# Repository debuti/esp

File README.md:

# esp
ESP8266 and ESP32 useful info, first steps and links to resources

Clone with $ git clone --recursive https://github.com/debuti/esp/

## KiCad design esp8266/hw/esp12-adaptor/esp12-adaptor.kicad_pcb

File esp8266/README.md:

# ESP8266 dev instructions
## Hardware used
 * ESP01 w/ 512KB flash
 * ESP01 flash adaptation PCB (green wire one)
 * ESP01 run adaptation PCB (blue and red wires)
 * FTDI cable set to 3.3v
 * USB to miniusb data cable
 * ESP12E w/ 4MB flash
 * ESP12E adaptation PCB
 * ESP12E flash adaptation PCB

## Test that the module is working ok

## Download and build the workenv: toolchain + RTOS SDK
### Download and build the toolchain
```
sudo apt-get install make unrar-free autoconf automake libtool gcc g++ gperf \
    flex bison texinfo gawk ncurses-dev libexpat-dev python-dev python python-serial \
    sed grep git unzip bash help2man wget bzip2 libtool-bin
git clone --recursive https://github.com/pfalcon/esp-open-sdk.git
cd esp-open-sdk
make toolchain esptool libhal STANDALONE=n
echo "export PATH=$PWD/xtensa-lx106-elf/bin:\$PATH" >> ~/.bashrc
cd -
sudo usermod -a -G dialout $USER
```

> You can just install esptool.py if you just plan to flash compiled binaries to esp. sudo pip install esptool

### Download and build the unofficial RTOS SDK
```
git clone --recursive https://github.com/Superhouse/esp-open-rtos.git
cd esp-open-rtos
```
Try to build a sample
```
make -j$(nproc) -C examples/http_get
```

### Download and build the official RTOS SDK
```
git clone https://github.com/espressif/ESP8266_RTOS_SDK.git
```

## Flash!
### ESP12 w/ adaptation pcb
 * Connect jumper in adaptation PCB: GPIO0 -> GND
 * Connect ESP12 to adaptation PCB
 * Connect VCC to 5v with given usb cord
 * Connect FTDI cable to adaptation PCB and to PC
 * Flash with ex: sudo esptool.py --port /dev/ttyUSB0 write_flash 0x00000 <.bin>

### ESP01 w/ flash adaptation pcb
 * Connect ESP01 to adaptation PCB
 * Connect FTDI cable to adaptation PCB and to PC
 * Flash with ex: sudo esptool.py --port /dev/ttyUSB0 write_flash 0x00000 <.bin> 

## Resources
* https://github.com/pfalcon/esp-open-sdk
* https://github.com/Superhouse/esp-open-rtos
* https://github.com/espressif/ESP8266_RTOS_SDK
* http://williamdurand.fr/2015/03/17/playing-with-a-esp8266-wifi-module/
* https://pixhawk.org/_media/peripherals/flashing_esp-01.png

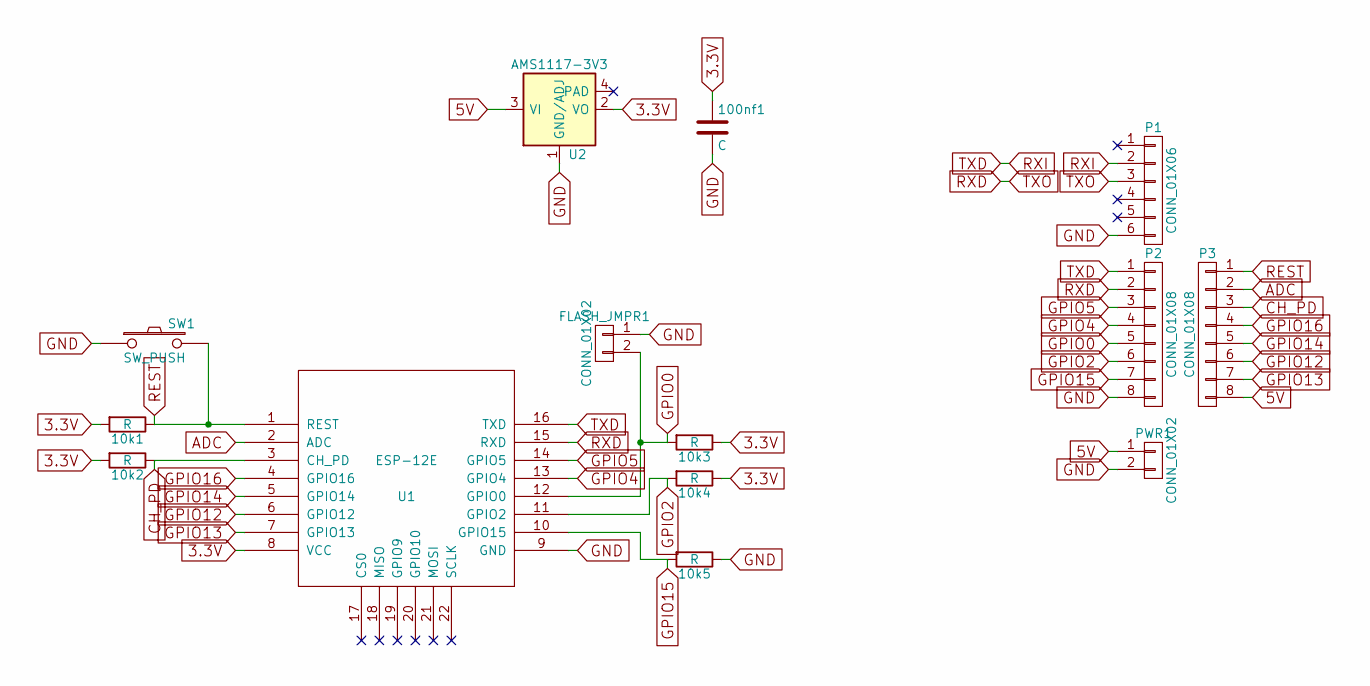
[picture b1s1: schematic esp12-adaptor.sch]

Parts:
10k1, 10k2, 10k3, 10k4, 10k5: R; R_0603_HandSoldering
100nf1: C; C_0603_HandSoldering
FLASH_JMPR1: CONN_01X02; Socket_Strip_Straight_1x02
P1: CONN_01X06; Pin_Header_Angled_1x06
P2, P3: CONN_01X08; Pin_Header_Straight_1x08
PWR1: CONN_01X02; Pin_Header_Straight_1x02
SW1: SW_PUSH; SW_SPST_EVPBF
U1: ESP-12E; ESP-12E_SMD
U2: AMS1117-3V3; SOT-223; MPN LM1117

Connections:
3.3V: 10k1.2, 10k2.2, 10k3.1, 10k4.1, 100nf1.1, U1.8 (VCC), U2.2 (VO)
5V: P3.8, PWR1.1, U2.3 (VI)
ADC: P3.2, U1.2 (ADC)
CH_PD: 10k2.1, P3.3, U1.3 (CH_PD)
GND: 10k5.1, 100nf1.2, FLASH_JMPR1.1, P1.6, P2.8, PWR1.2, SW1.1, U1.9 (GND), U2.1 (GND/ADJ)
GPIO0: 10k3.2, FLASH_JMPR1.2, P2.5, U1.12 (GPIO0)
GPIO2: 10k4.2, P2.6, U1.11 (GPIO2)
GPIO4: P2.4, U1.13 (GPIO4)
GPIO5: P2.3, U1.14 (GPIO5)
GPIO12: P3.6, U1.6 (GPIO12)
GPIO13: P3.7, U1.7 (GPIO13)
GPIO14: P3.5, U1.5 (GPIO14)
GPIO15: 10k5.2, P2.7, U1.10 (GPIO15)
GPIO16: P3.4, U1.4 (GPIO16)
REST: 10k1.1, P3.1, SW1.2, U1.1 (REST)
RXD: P1.3, P2.2, U1.15 (RXD)
RXI: P1.2, P2.1, U1.16 (TXD)

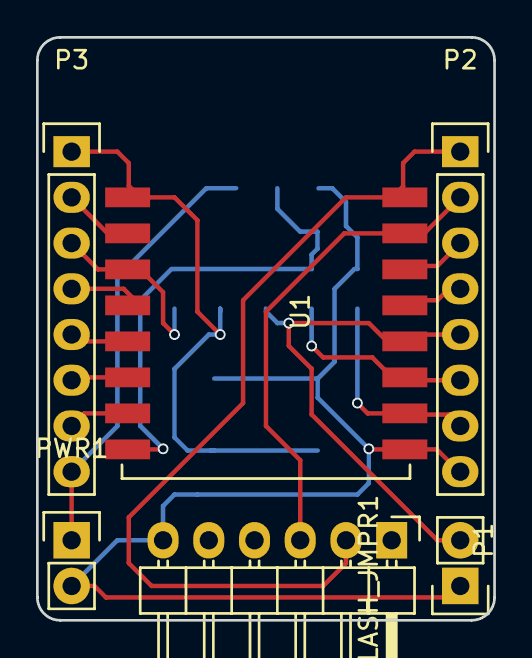
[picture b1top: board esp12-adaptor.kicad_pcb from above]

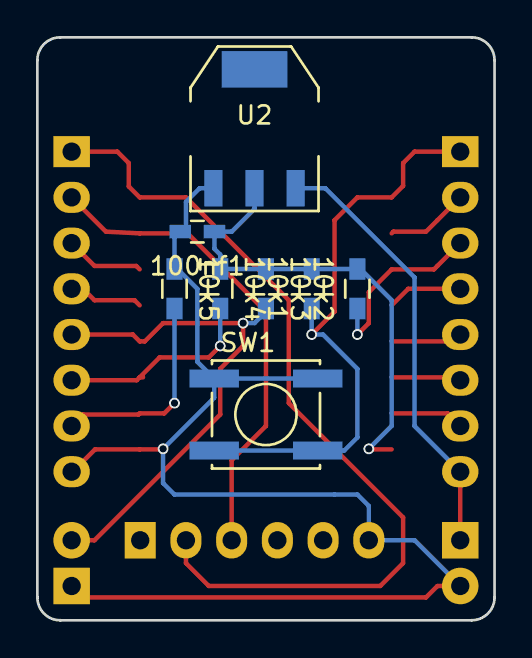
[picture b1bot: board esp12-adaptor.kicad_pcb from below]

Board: 2 copper layers, 25.4 x 32.4 mm, 14 parts (8 on the bottom side), 17 nets.

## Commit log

2018-04-01 First
2018-04-05 Updated esp8266 README.md
2018-10-05 Added sch for custom esp12 module
2018-10-05 Linked projects
2018-10-05 Minor
